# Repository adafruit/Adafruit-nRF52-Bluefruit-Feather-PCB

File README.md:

# Adafruit-nRF52-Bluefruit-Feather-PCB

PCB files for the Adafruit nRF52 Bluefruit Feather and the Adafruit
nRF52840 Feather Express.

Format is EagleCAD schematic and board layout.

These boards were designed before we spent effort on low power and are not intended for low power usage.

For more details, check out the product page at

    * https://www.adafruit.com/product/3406 (nRF52832)
    * https://www.adafruit.com/product/4062 (nRF52840)

Adafruit invests time and resources providing this open source design,
please support Adafruit and open-source hardware by purchasing
products from Adafruit!

Designed by Adafruit Industries.  
Creative Commons Attribution, Share-Alike license, check license.txt for more information
All text above must be included in any redistribution

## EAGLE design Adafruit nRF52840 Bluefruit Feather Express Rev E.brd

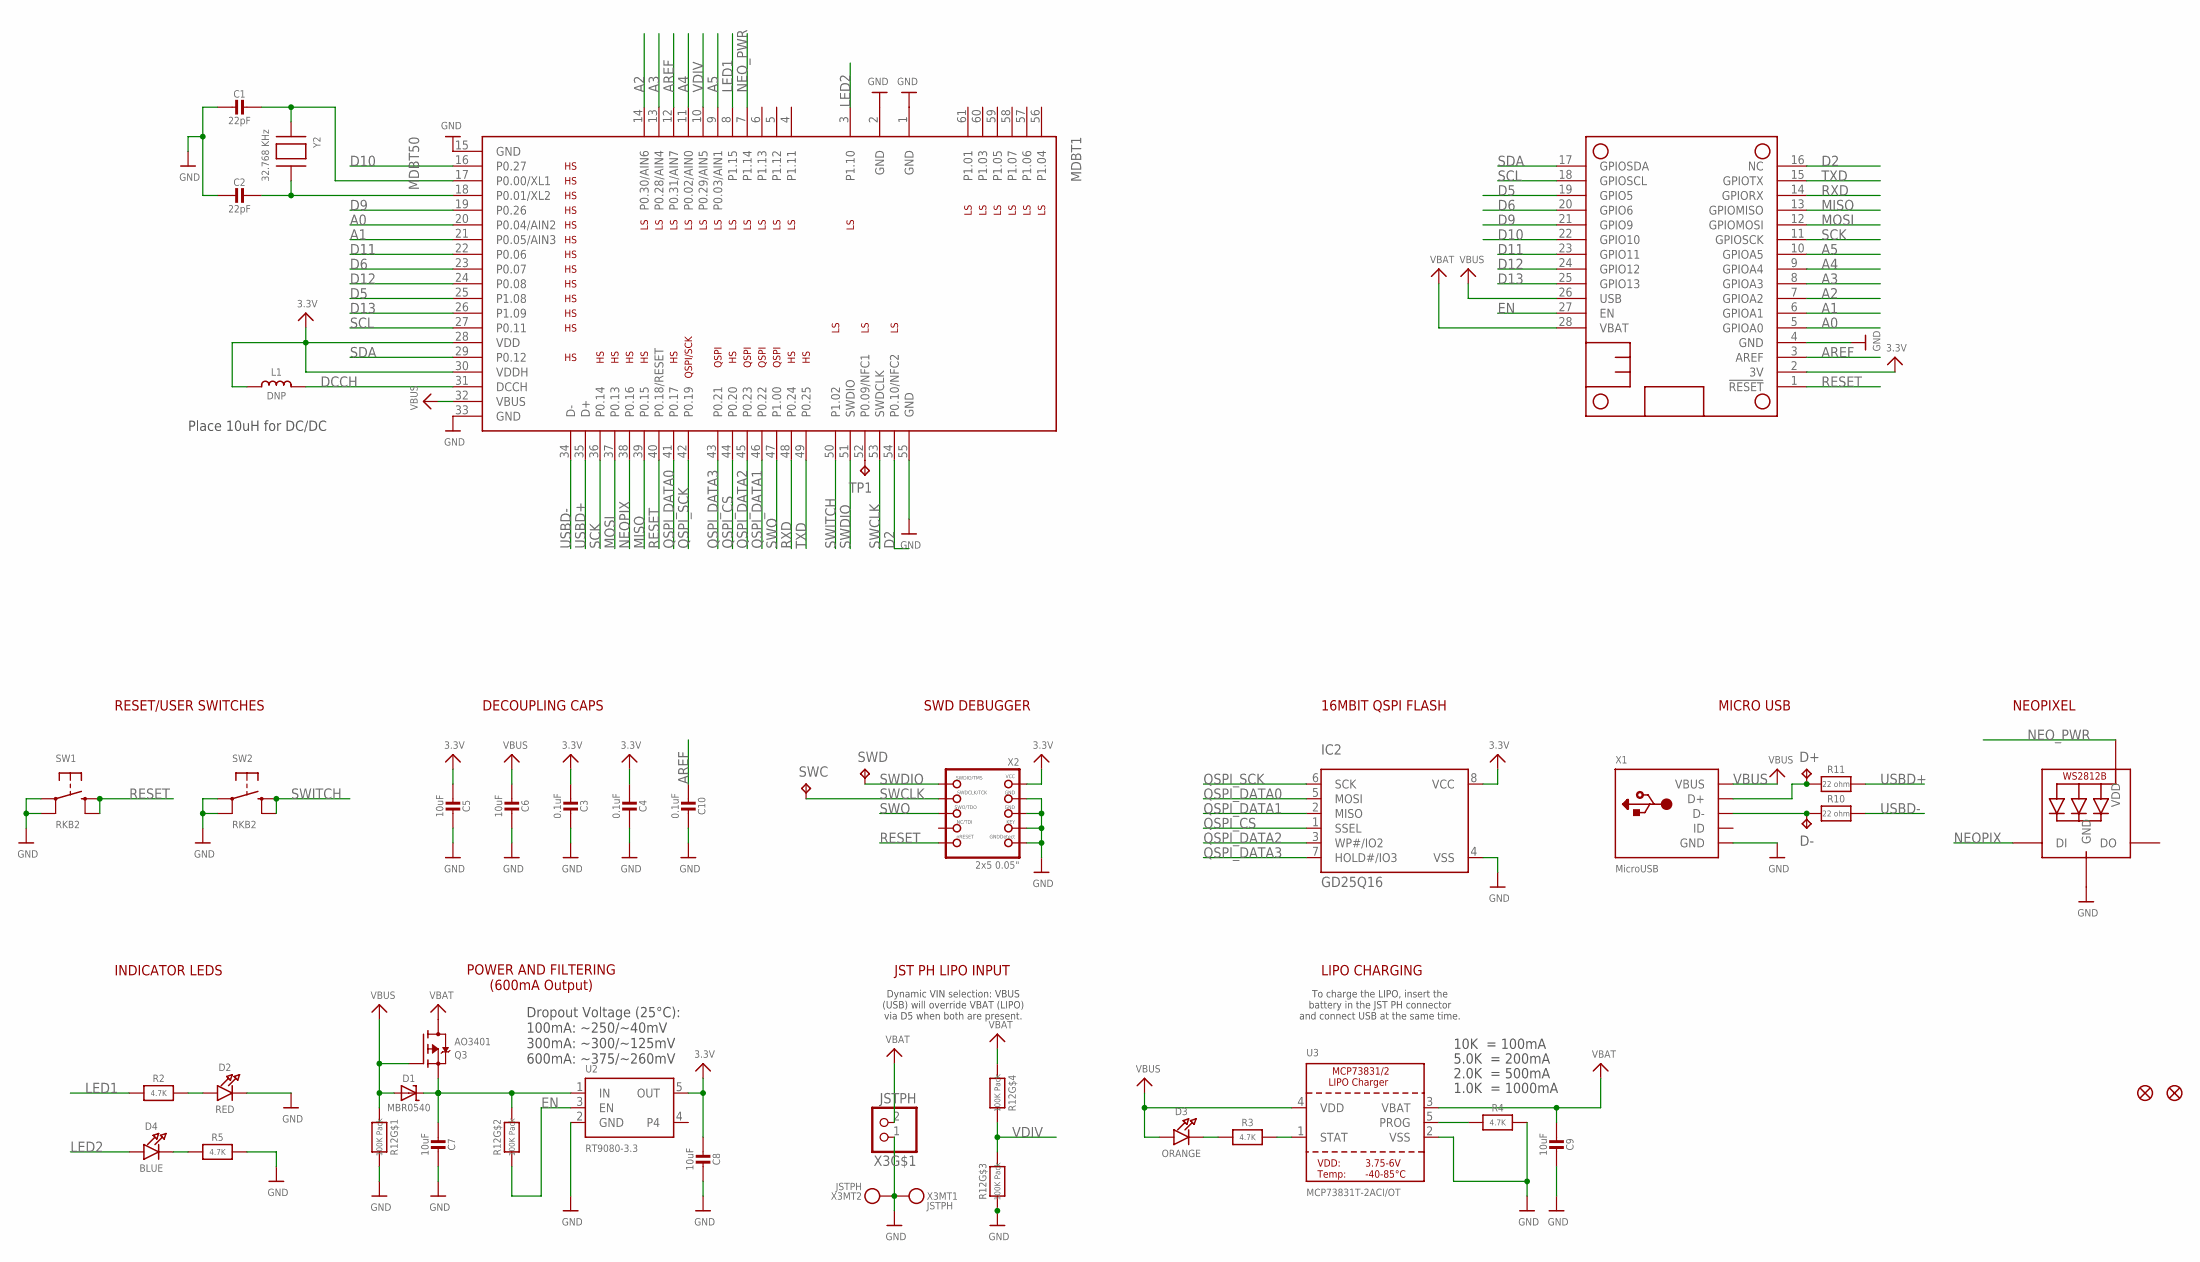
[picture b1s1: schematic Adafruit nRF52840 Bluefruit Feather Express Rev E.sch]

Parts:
C1, C2: 22pF; 0603-NO
C3, C4, C10: 0.1uF; 0603-NO
C5, C6, C7, C8, C9: 10uF; 0805-NO
D1: MBR0540; SOD-123
D2: RED; CHIPLED_0603_NOOUTLINE
D3: ORANGE; CHIPLED_0603_NOOUTLINE
D4: BLUE; CHIPLED_0603_NOOUTLINE
D+: TPTP10R; TP10R
D-: TPTP10R; TP10R
FID1, FID2: FIDUCIAL_1MM
IC2: GD25Q16; USON8
L1: DNP; _0805MP
LED1: WS2812B_3535FULL; LED3535_FULLPADS
MDBT1: MDBT50
MS1: FEATHERWING_NODIM
Q3: AO3401; SOT23-R
R2, R3, R4, R5: 4.7K; 0603-NO
R10, R11: 22 ohm; _0603MP
R12: 100K Pack; RESPACK_4X0603
SW1, SW2: RKB2; BTN_RKB2_4.6X2.8
SWC: TPTP12R; TP12R
SWD: TPTP12R; TP12R
TP1: TPTP10R; TP10R
U2: RT9080-3.3; SOT23-5; JLC_ROTATION 0
U3: MCP73831T-2ACI/OT; SOT23-5
X1: MicroUSB; 4UCONN_20329_V2
X2: 2x5 0.05"; 2X05_1.27MM_BOX_POSTS
X3: JSTPH; JSTPH2_BATT
Y2: 32.768 KHz; XTAL3215

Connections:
3.3V: C3.2, C4.2, C5.2, C8.2, IC2.8 (VCC), L1.1, MDBT1.28 (VDD), MDBT1.30 (VDDH), MS1.2 (3V), U2.5 (OUT), X2.1 (VCC)
A0: MDBT1.20 (P0.04/AIN2), MS1.5 (GPIOA0)
A1: MDBT1.21 (P0.05/AIN3), MS1.6 (GPIOA1)
A2: MDBT1.14 (P0.30/AIN6), MS1.7 (GPIOA2)
A3: MDBT1.13 (P0.28/AIN4), MS1.8 (GPIOA3)
A4: MDBT1.11 (P0.02/AIN0), MS1.9 (GPIOA4)
A5: MDBT1.9 (P0.03/AIN1), MS1.10 (GPIOA5)
AREF: C10.2, MDBT1.12 (P0.31/AIN7), MS1.3 (AREF)
D2: MDBT1.54 (P0.10/NFC2), MS1.16 (NC)
D5: MDBT1.25 (P1.08), MS1.19 (GPIO5)
D6: MDBT1.23 (P0.07), MS1.20 (GPIO6)
D9: MDBT1.19 (P0.26), MS1.21 (GPIO9)
D10: MDBT1.16 (P0.27), MS1.22 (GPIO10)
D11: MDBT1.22 (P0.06), MS1.23 (GPIO11)
D12: MDBT1.24 (P0.08), MS1.24 (GPIO12)
D13: MDBT1.26 (P1.09), MS1.25 (GPIO13)
D+: D+.TP, R11.1, X1.D+
D-: D-.TP, R10.1, X1.D-
DCCH: L1.2, MDBT1.31 (DCCH)
EN: MS1.27 (EN), R12.2 (1), U2.3 (EN)
GND: C1.2, C2.2, C3.1, C4.1, C5.1, C6.1, C7.1, C8.1, C9.1, C10.1, D2.C, IC2.4 (VSS), LED1.4 (GND), MDBT1.1 (GND), MDBT1.2 (GND), MDBT1.15 (GND), MDBT1.33 (GND), MDBT1.55 (GND), MS1.4 (GND), R4.2, R5.2, R12.3 (1), R12.8 (2), SW1.A, SW1.A' (P1), SW2.A, SW2.A' (P1), U2.2 (GND), U3.2 (VSS), X1.BASE@1 (GND), X1.BASE@2 (GND), X1.GND, X1.SPRT@1 (GND), X1.SPRT@2 (GND), X1.SPRT@3 (GND), X1.SPRT@4 (GND), X2.3 (GND), X2.5 (GND), X2.7 (KEY), X2.9 (GNDDETECT), X3.1, X3.NC1, X3.NC2
LED1: MDBT1.8 (P1.15), R2.1
LED2: D4.A, MDBT1.3 (P1.10)
MISO: MDBT1.39 (P0.15), MS1.13 (GPIOMISO)
MOSI: MDBT1.37 (P0.13), MS1.12 (GPIOMOSI)
unnamed: D3.C, R3.1
unnamed: D2.A, R2.2
unnamed: C1.1, MDBT1.17 (P0.00/XL1), Y2.P$1
unnamed: C2.1, MDBT1.18 (P0.01/XL2), Y2.P$2
unnamed: R3.2, U3.1 (STAT)
unnamed: R4.1, U3.5 (PROG)
unnamed: D4.C, R5.1
NEOPIX: LED1.1 (DI), MDBT1.38 (P0.16)
NEO_PWR: LED1.2 (VDD), MDBT1.7 (P1.14)
NFC2: MDBT1.52 (P0.09/NFC1), TP1.TP
QSPI_CS: IC2.1 (SSEL), MDBT1.44 (P0.20)
QSPI_DATA0: IC2.5 (MOSI), MDBT1.41 (P0.17)
QSPI_DATA1: IC2.2 (MISO), MDBT1.46 (P0.22)
QSPI_DATA2: IC2.3 (WP#/IO2), MDBT1.45 (P0.23)
QSPI_DATA3: IC2.7 (HOLD#/IO3), MDBT1.43 (P0.21)
QSPI_SCK: IC2.6 (SCK), MDBT1.42 (P0.19)
RESET: MDBT1.40 (P0.18/RESET), MS1.1 (!RESET), SW1.B (S), SW1.B' (S1), X2.10 (NRESET)
RXD: MDBT1.48 (P0.24), MS1.14 (GPIORX)
SCK: MDBT1.36 (P0.14), MS1.11 (GPIOSCK)
SCL: MDBT1.27 (P0.11), MS1.18 (GPIOSCL)
SDA: MDBT1.29 (P0.12), MS1.17 (GPIOSDA)
SWCLK: MDBT1.53 (SWDCLK), SWC.TP, X2.4 (SWDCLK)
SWDIO: MDBT1.51 (SWDIO), SWD.TP, X2.2 (SWDIO)
SWITCH: MDBT1.50 (P1.02), SW2.B (S), SW2.B' (S1)
SWO: MDBT1.47 (P1.00), X2.6 (SWO)
TXD: MDBT1.49 (P0.25), MS1.15 (GPIOTX)
USBD+: MDBT1.35 (D+), R11.2
USBD-: MDBT1.34 (D-), R10.2
VBAT: C9.2, MS1.28 (VBAT), Q3.3 (D), R12.4 (1), U3.3 (VBAT), X3.2
VBUS: C6.2, D1.A, D3.A, MDBT1.32 (VBUS), MS1.26 (USB), Q3.1 (G), R12.1, U3.4 (VDD), X1.VBUS
VDIV: MDBT1.10 (P0.29/AIN5), R12.5 (2), R12.6 (2)
VHI: C7.2, D1.C, Q3.2 (S), R12.7 (2), U2.1 (IN)

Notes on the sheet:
10K = 100mA
5.0K = 200mA
2.0K = 500mA
1.0K = 1000mA
LIPO CHARGING
To charge the LIPO, insert the battery in the JST PH connector and connect USB at the same time.
POWER AND FILTERING (600mA Output)
JST PH LIPO INPUT
Dynamic VIN selection: VBUS (USB) will override VBAT (LIPO) via D5 when both are present.
Dropout Voltage (25°C): 100mA: ~250/~40mV 300mA: ~300/~125mV 600mA: ~375/~260mV
INDICATOR LEDS
RESET/USER SWITCHES
DECOUPLING CAPS
SWD DEBUGGER
16MBIT QSPI FLASH
MICRO USB
NEOPIXEL
Place 10uH for DC/DC

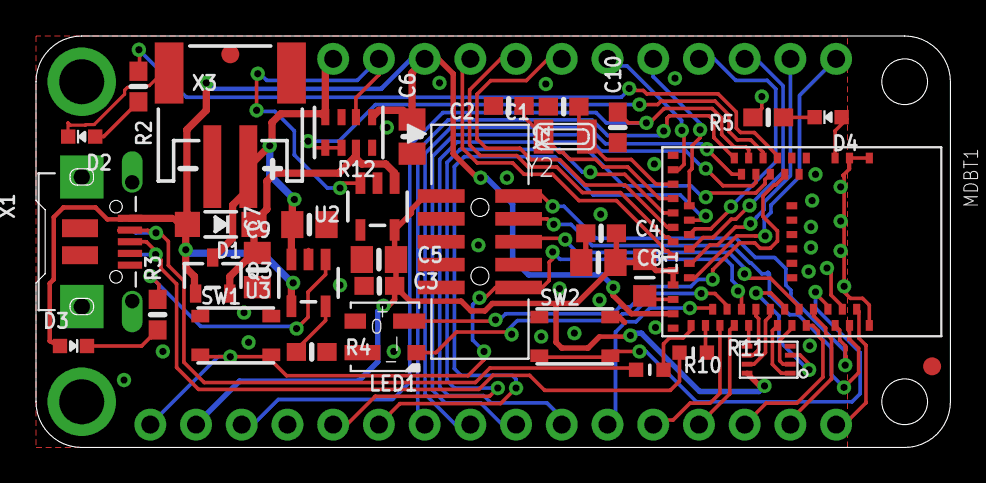
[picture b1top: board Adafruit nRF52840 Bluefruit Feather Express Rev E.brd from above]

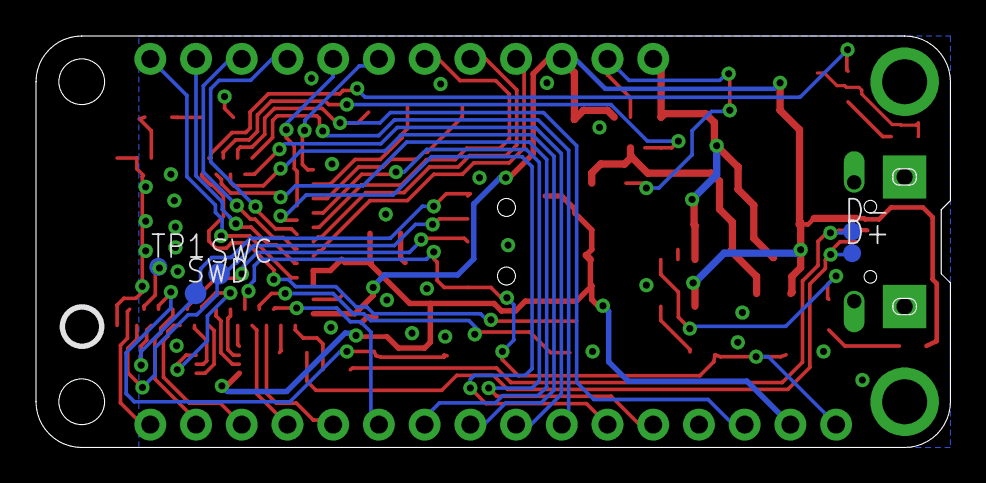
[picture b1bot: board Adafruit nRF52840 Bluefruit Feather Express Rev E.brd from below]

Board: 2 copper layers, 50.8 x 22.9 mm, 45 parts (7 on the bottom side), 57 nets.

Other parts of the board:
U$10: PCBFEAT-REV-056
U$12: NRF52840_BOT
U$14: NRF52840_TOP

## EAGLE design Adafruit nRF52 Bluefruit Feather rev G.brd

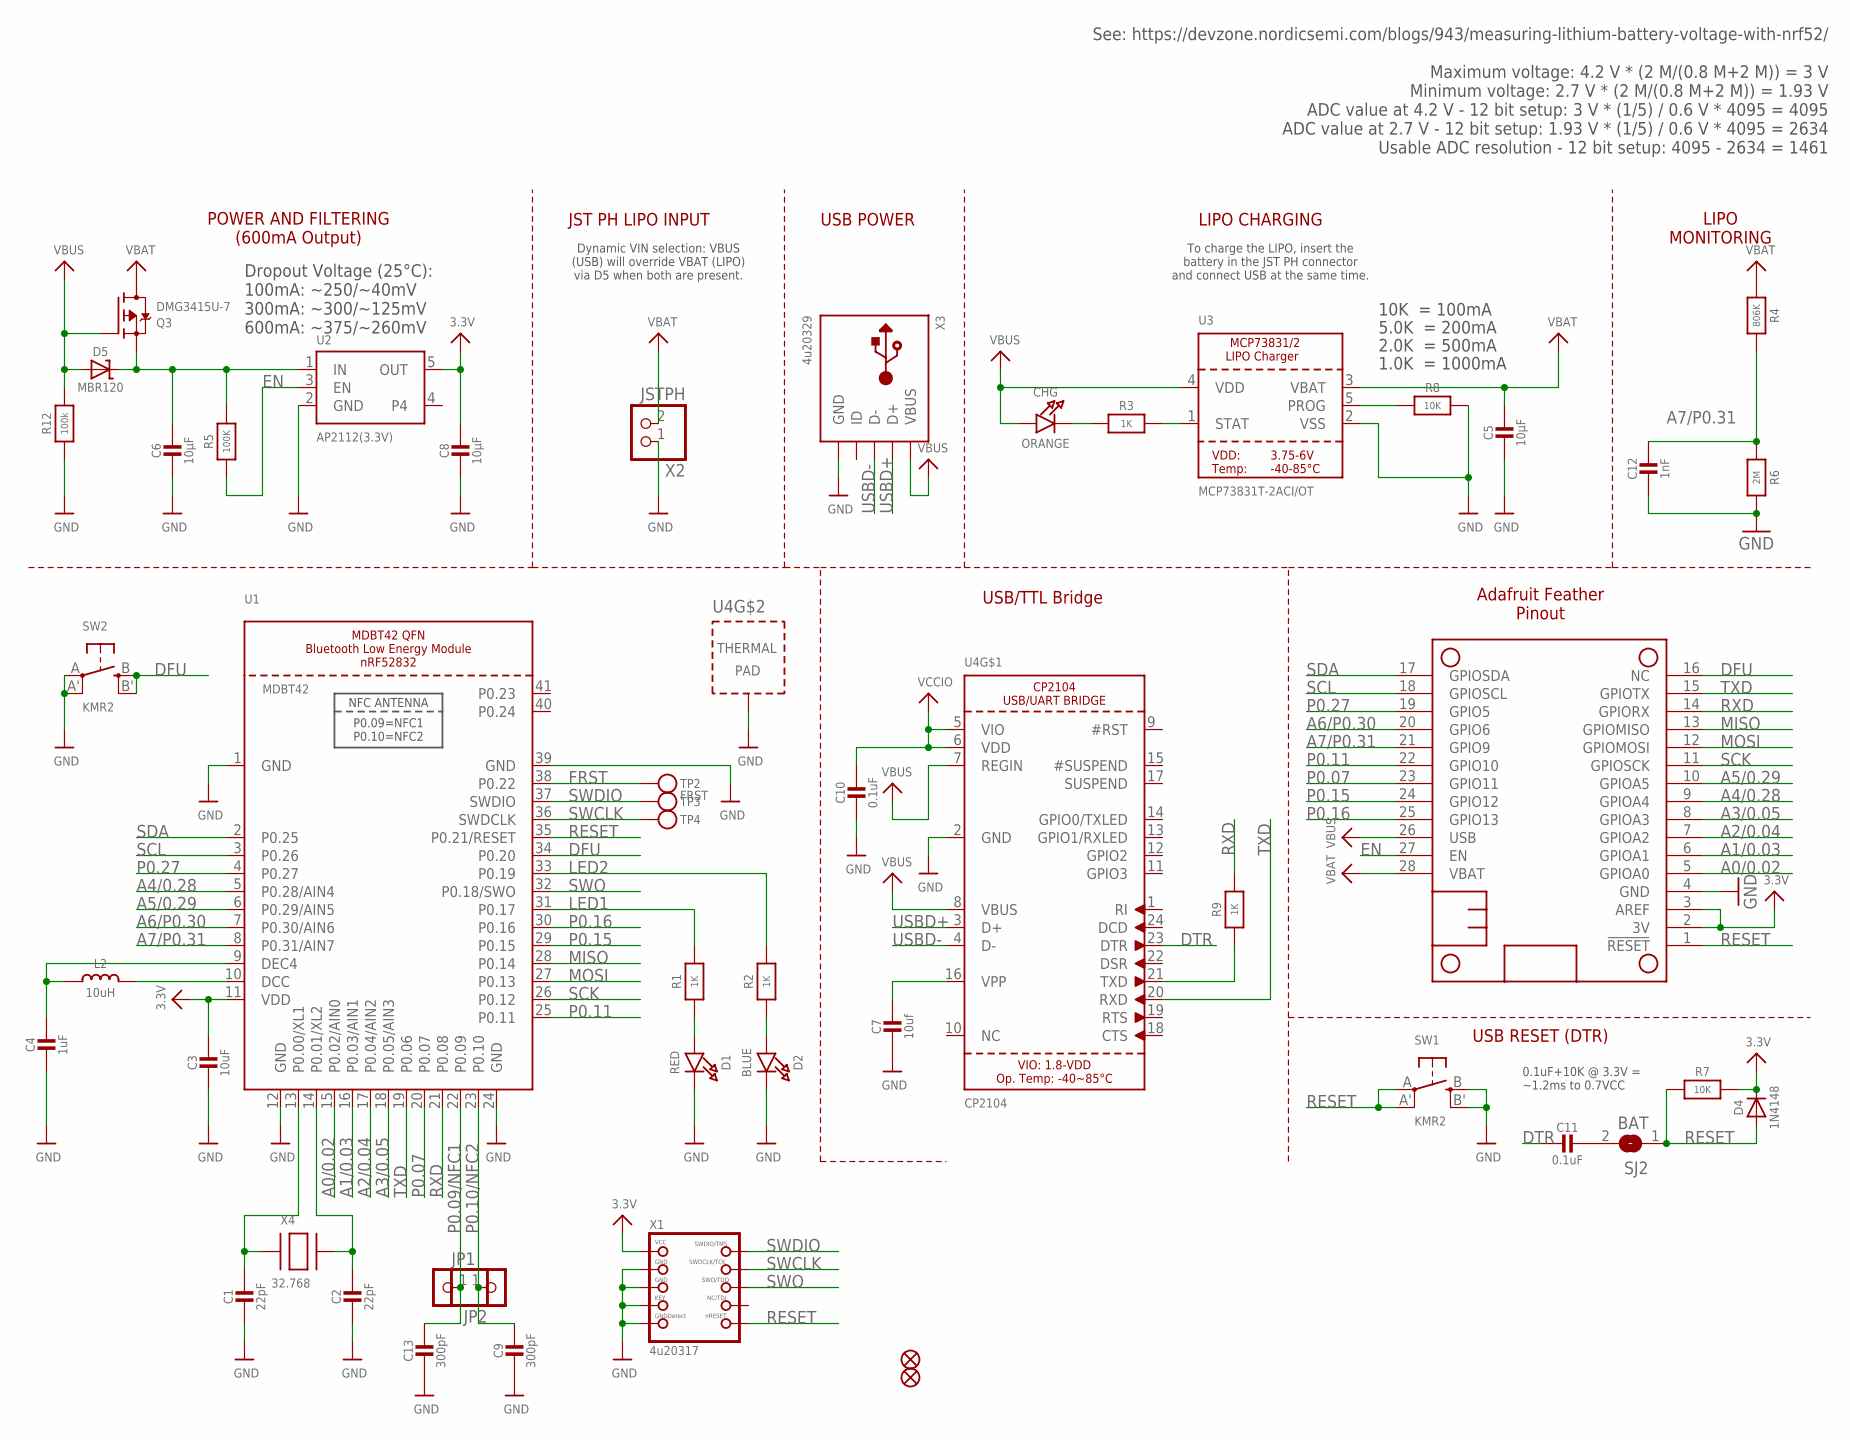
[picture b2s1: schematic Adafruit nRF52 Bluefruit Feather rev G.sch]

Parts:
C1, C2: 22pF; 0603-NO
C3: 10uF; 0805-NO
C4: 1uF; 0603-NO
C5, C6, C8: 10µF; 0805-NO
C7: 10uf; 0805-NO
C9, C13: 300pF; _0603MP
C10, C11: 0.1uF; 0603-NO
C12: 1nF; 0603-NO
CHG: ORANGE; CHIPLED_0805_NOOUTLINE
D1: RED; CHIPLED_0805_NOOUTLINE
D2: BLUE; CHIPLED_0805_NOOUTLINE
D4: 1N4148; SOD-323
D5: MBR120; SOD-123
FID1, FID3: FIDUCIAL_1MM
JP1, JP2: HEADER-1X12MM; 1X01_2MM
L2: 10uH; 0805-NO
MS1: FEATHERWING_NODIM
Q3: DMG3415U-7; SOT23-R
R1, R2, R3, R9: 1K; 0603-NO
R4: 806K; 0603-NO
R5: 100K; 0603-NO
R6: 2M; 0603-NO
R7, R8: 10K; 0603-NO
R12: 100k; 0603-NO
SJ2: BAT; SOLDERJUMPER_CLOSEDWIRE
SW1, SW2: KMR2; BTN_KMR2_4.6X2.8
TP2: FRST; PAD-1.5X2.0
TP3, TP4: TESTPOINTROUND2MM; TESTPOINT_ROUND_2MM
U1: MDBT42; BLE_MODULE_RAYTAC_MDBT42
U2: AP2112(3.3V); SOT23-5
U3: MCP73831T-2ACI/OT; SOT23-5
U4: CP2104; QFN24_4MM_SMSC
X1: 4u20317; 2X05_1.27MM_BOX_POSTS
X2: JSTPH; JSTPH2
X3: 4u20329; 4UCONN_20329_V2
X4: 32.768; XTAL3215

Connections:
3.3V: C3.1, C8.1, D4.C, MS1.2 (3V), MS1.3 (AREF), R7.2, U1.11 (VDD), U2.5 (OUT), X1.1 (VCC)
A0/0.02: MS1.5 (GPIOA0), U1.15 (P0.02/AIN0)
A1/0.03: MS1.6 (GPIOA1), U1.16 (P0.03/AIN1)
A2/0.04: MS1.7 (GPIOA2), U1.17 (P0.04/AIN2)
A3/0.05: MS1.8 (GPIOA3), U1.18 (P0.05/AIN3)
A4/0.28: MS1.9 (GPIOA4), U1.5 (P0.28/AIN4)
A5/0.29: MS1.10 (GPIOA5), U1.6 (P0.29/AIN5)
A6/P0.30: MS1.20 (GPIO6), U1.7 (P0.30/AIN6)
A7/P0.31: C12.1, MS1.21 (GPIO9), R4.2, R6.1, U1.8 (P0.31/AIN7)
DFU: MS1.16 (NC), SW2.B (S), SW2.B' (S1), U1.34 (P0.20)
DTR: C11.2, U4.23 (DTR)
EN: MS1.27 (EN), R5.1, U2.3 (EN)
FRST: TP2.P$1, U1.38 (P0.22)
GND: C1.2, C2.2, C3.2, C4.2, C5.2, C6.2, C7.2, C8.2, C9.2, C10.2, C12.2, C13.2, D1.C, D2.C, MS1.4 (GND), R6.2, R8.2, R12.1, SW1.B (S), SW1.B' (S1), SW2.A, SW2.A' (P1), U1.1 (GND), U1.12 (GND), U1.24 (GND), U1.39 (GND), U2.2 (GND), U3.2 (VSS), U4.2 (GND), U4.THERM (TP), X1.3 (GND), X1.5 (GND), X1.7 (KEY), X1.9 (GNDDETECT), X2.1, X3.BASE@1 (GND), X3.BASE@2 (GND), X3.GND, X3.SPRT@1 (GND), X3.SPRT@2 (GND), X3.SPRT@3 (GND), X3.SPRT@4 (GND)
LED1: R1.2, U1.31 (P0.17)
LED2: R2.2, U1.33 (P0.19)
MISO: MS1.13 (GPIOMISO), U1.28 (P0.14)
MOSI: MS1.12 (GPIOMOSI), U1.27 (P0.13)
unnamed: C1.1, U1.13 (P0.00/XL1), X4.P$1
unnamed: C2.1, U1.14 (P0.01/XL2), X4.P$2
unnamed: L2.2, U1.10 (DCC)
unnamed: CHG.C, R3.1
unnamed: D1.A, R1.1
unnamed: D2.A, R2.1
unnamed: C4.1, L2.1, U1.9 (DEC4)
unnamed: R3.2, U3.1 (STAT)
unnamed: R8.1, U3.5 (PROG)
unnamed: R9.1, U4.21 (TXD)
unnamed: C11.1, SJ2.2
unnamed: C7.1, U4.16 (VPP)
P0.07: MS1.23 (GPIO11), U1.20 (P0.07)
P0.09/NFC1: C13.1, JP2.1, U1.22 (P0.09)
P0.10/NFC2: C9.1, JP1.1, U1.23 (P0.10)
P0.11: MS1.22 (GPIO10), U1.25 (P0.11)
P0.15: MS1.24 (GPIO12), U1.29 (P0.15)
P0.16: MS1.25 (GPIO13), U1.30 (P0.16)
P0.27: MS1.19 (GPIO5), U1.4 (P0.27)
RESET: D4.A, MS1.1 (!RESET), R7.1, SJ2.1, SW1.A, SW1.A' (P1), U1.35 (P0.21/RESET), X1.10 (NRESET)
RXD: MS1.14 (GPIORX), R9.2, U1.21 (P0.08)
SCK: MS1.11 (GPIOSCK), U1.26 (P0.12)
SCL: MS1.18 (GPIOSCL), U1.3 (P0.26)
SDA: MS1.17 (GPIOSDA), U1.2 (P0.25)
SWCLK: TP4.P$1, U1.36 (SWDCLK), X1.4 (SWDCLK)
SWDIO: TP3.P$1, U1.37 (SWDIO), X1.2 (SWDIO)
SWO: U1.32 (P0.18/SWO), X1.6 (SWO)
TXD: MS1.15 (GPIOTX), U1.19 (P0.06), U4.20 (RXD)
USBD+: U4.3 (D+), X3.D+
USBD-: U4.4 (D-), X3.D-
VBAT: C5.1, MS1.28 (VBAT), Q3.3 (D), R4.1, U3.3 (VBAT), X2.2
VBUS: CHG.A, D5.A, MS1.26 (USB), Q3.1 (G), R12.2, U3.4 (VDD), U4.7 (REGIN), U4.8 (VBUS), X3.VBUS
VCCIO: C10.1, U4.5 (VIO), U4.6 (VDD)
VIN: C6.1, D5.C, Q3.2 (S), R5.2, U2.1 (IN)

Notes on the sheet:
10K = 100mA
5.0K = 200mA
2.0K = 500mA
1.0K = 1000mA
LIPO CHARGING
LIPO MONITORING
To charge the LIPO, insert the battery in the JST PH connector and connect USB at the same time.
POWER AND FILTERING (600mA Output)
JST PH LIPO INPUT
Dynamic VIN selection: VBUS (USB) will override VBAT (LIPO) via D5 when both are present.
Dropout Voltage (25°C): 100mA: ~250/~40mV 300mA: ~300/~125mV 600mA: ~375/~260mV
USB POWER
USB/TTL Bridge
Adafruit Feather Pinout
See: https://devzone.nordicsemi.com/blogs/943/measuring-lithium-battery-voltage-with-nrf52/ Maximum voltage: 4.2 V * (2 M/(0.8 M+2 M)) = 3 V Minimum voltage: 2.7 V * (2 M/(0.8 M+2 M)) = 1.93 V ADC value at 4.2 V - 12 bit setup: 3 V * (1/5) / 0.6 V * 4095 = 4095 ADC value at 2.7 V - 12 bit setup: 1.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
USB RESET (DTR)
0.1uF+10K @ 3.3V = ~1.2ms to 0.7VCC

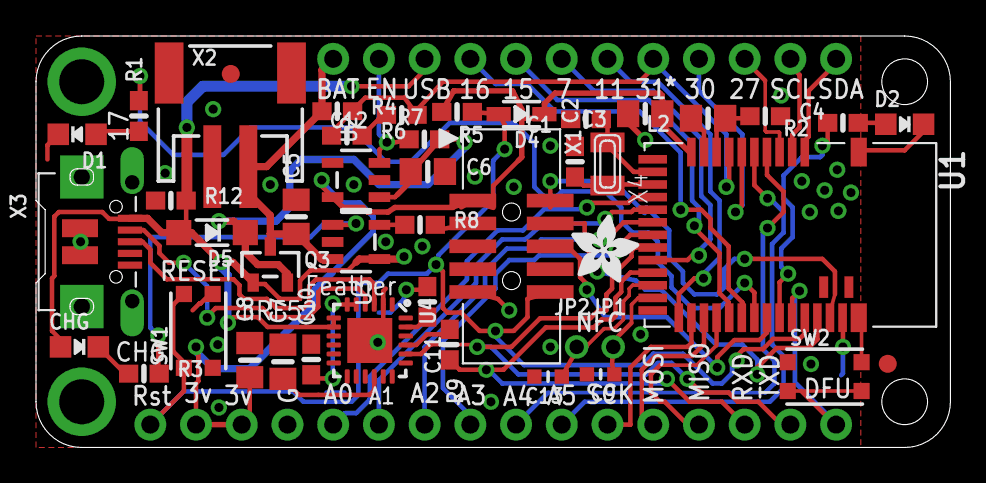
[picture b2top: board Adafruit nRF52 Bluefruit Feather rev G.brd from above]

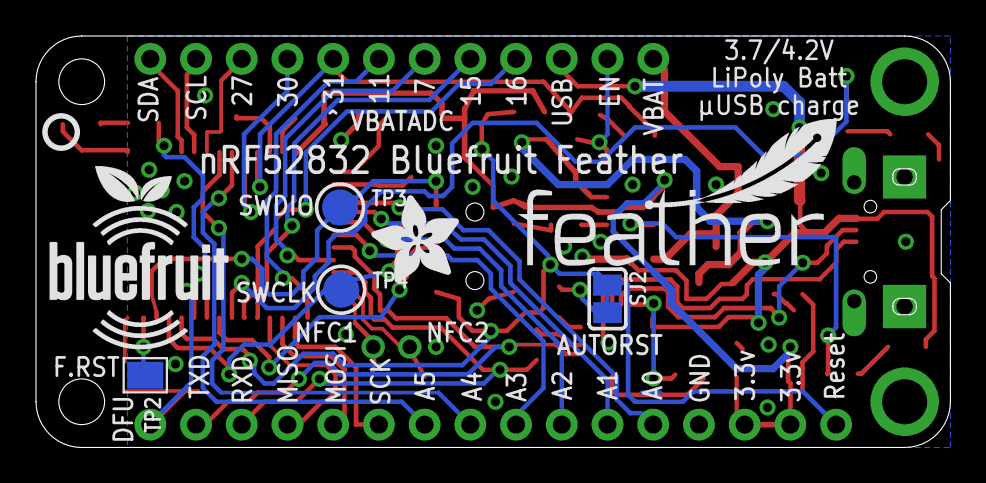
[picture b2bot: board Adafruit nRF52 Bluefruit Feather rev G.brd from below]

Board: 2 copper layers, 50.8 x 22.9 mm, 54 parts (8 on the bottom side), 52 nets.

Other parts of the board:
U$17: PCBFEAT-REV-040
U$45: BLUEFRUITLOGO_100MM
U$46: FEATHERLOGO_MED
U$47: ADAFRUIT_5MM
U$49: ADAFRUIT_3.5MM

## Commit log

2017-03-22 init
2018-11-08 https://github.com/adafruit/Adafruit-nRF52-Bluefruit-Feather-PCB/issues/1
2019-01-02 Added nRF52840 Feather Express
2019-01-02 File rename
2021-05-15 Add pin reference PDF
2023-12-16 Fixing typo: D5 -> D1
2025-05-05 adding nrf52840 feather rev E

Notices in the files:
parts and their libraries:
microbuilder: This work is placed in the public domain, and may be freely used for commercial and non-commercial work with the following conditions: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
